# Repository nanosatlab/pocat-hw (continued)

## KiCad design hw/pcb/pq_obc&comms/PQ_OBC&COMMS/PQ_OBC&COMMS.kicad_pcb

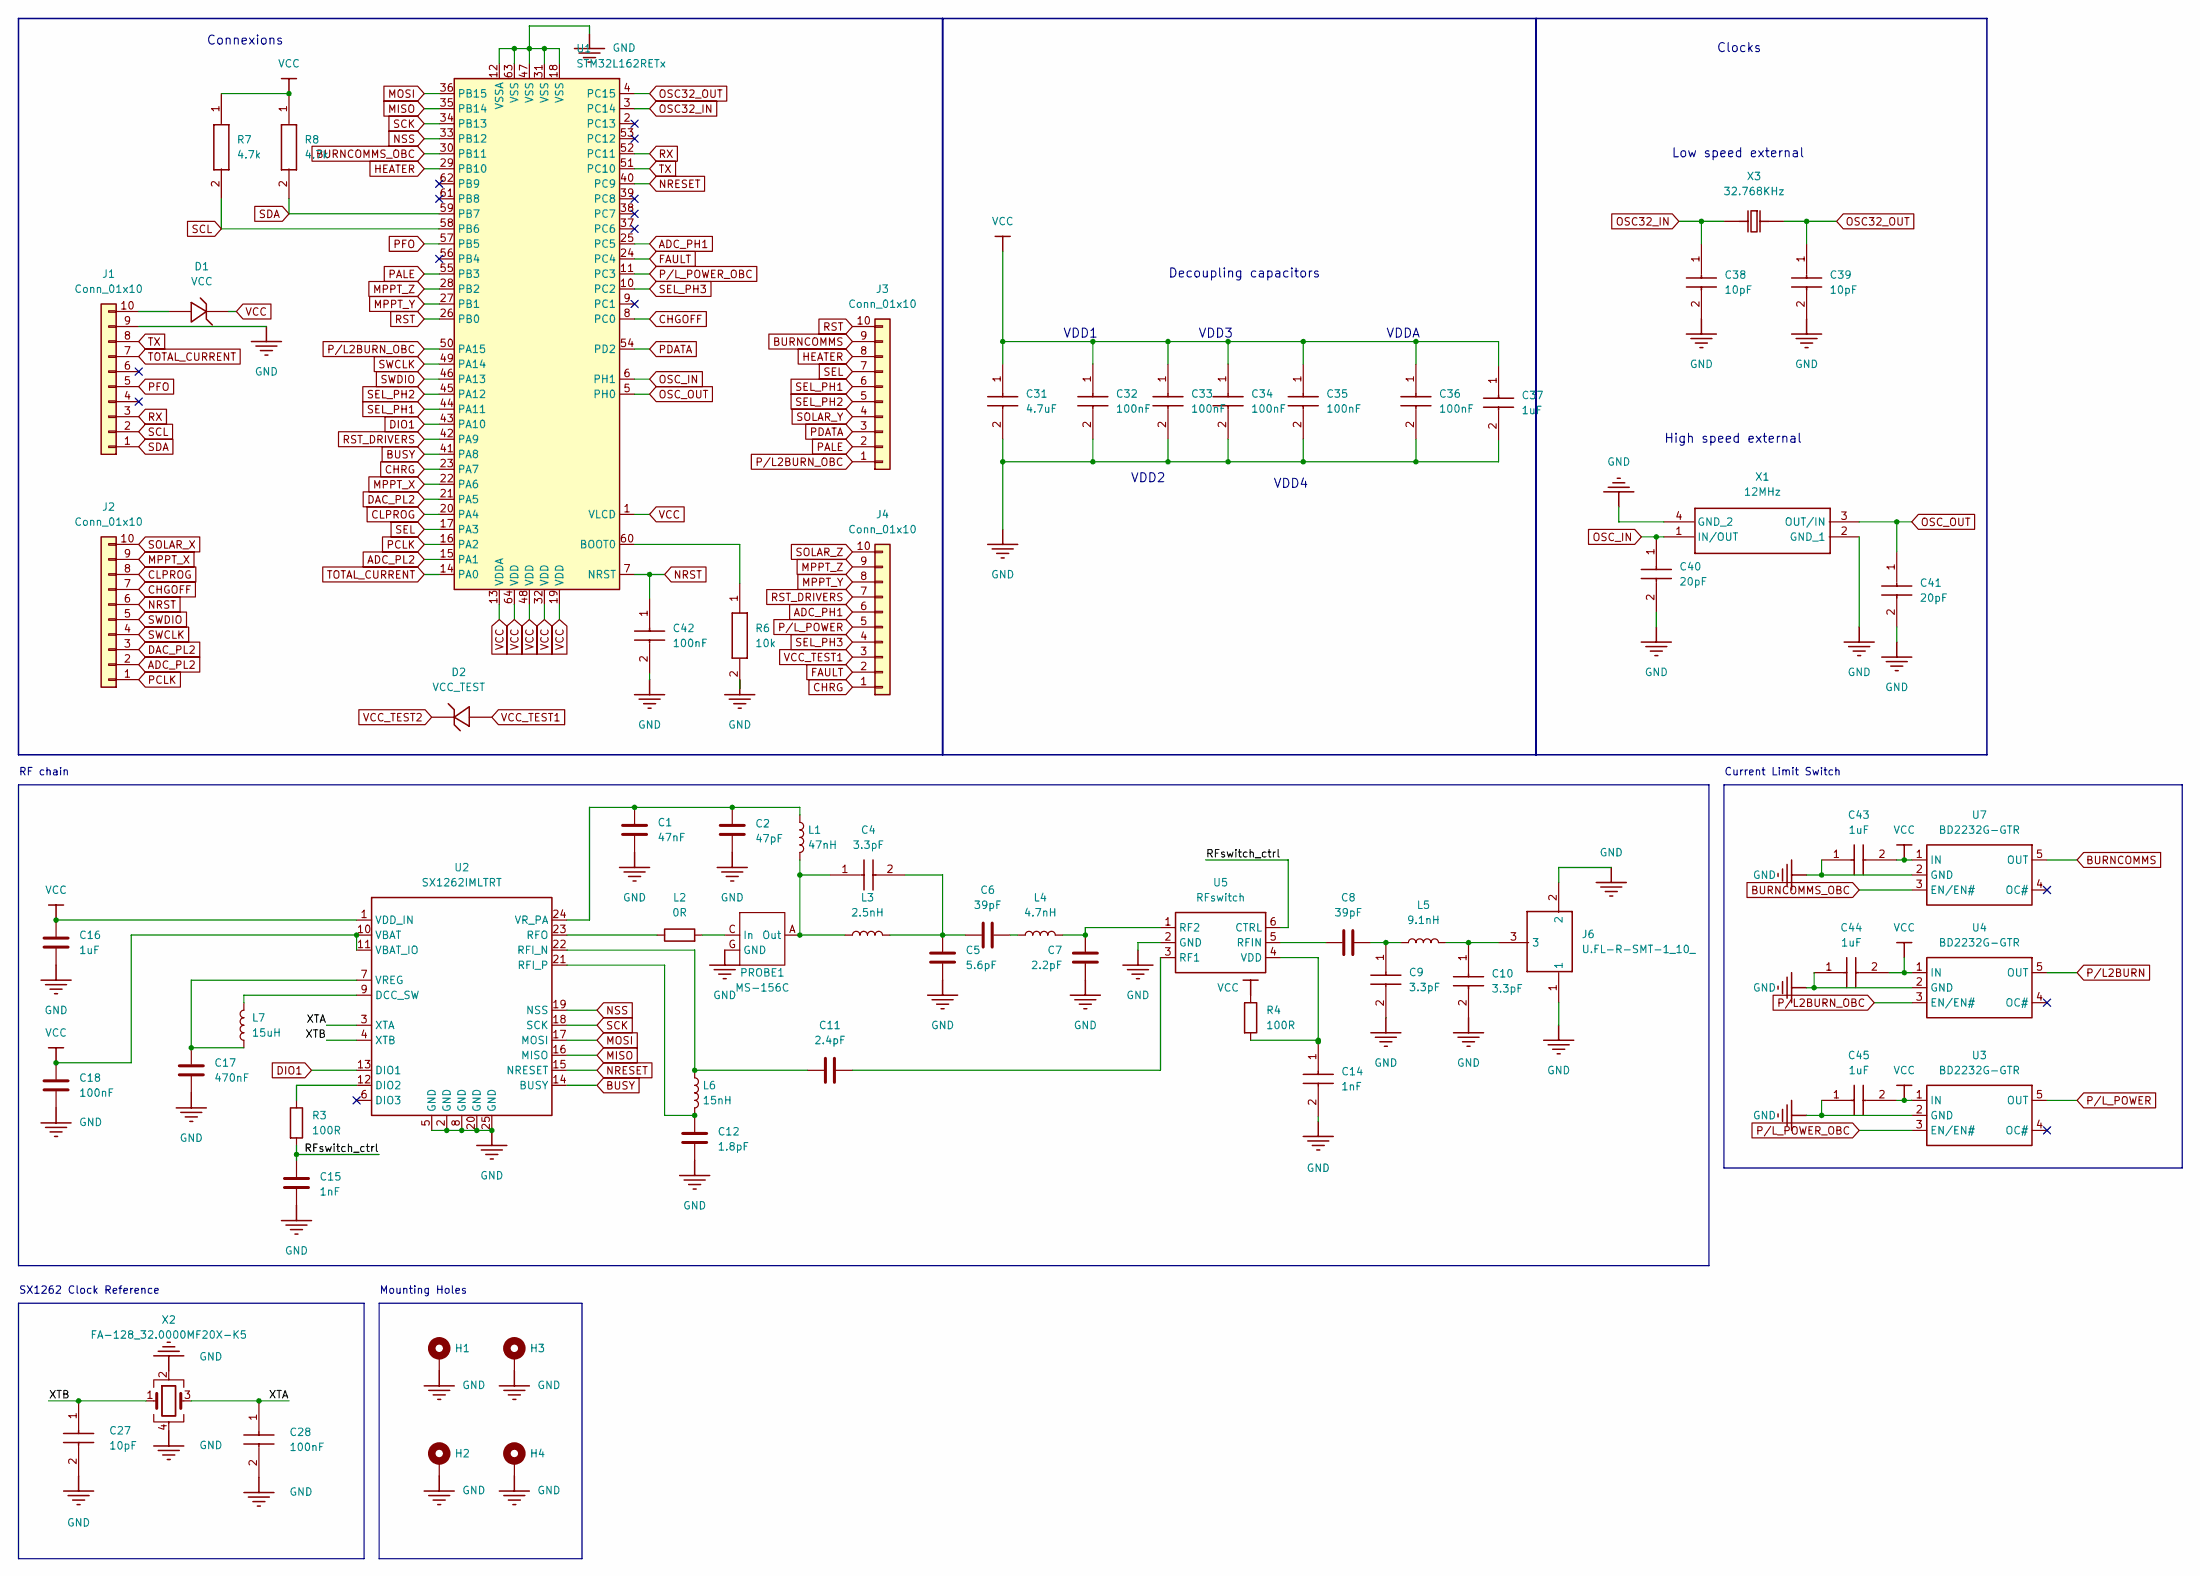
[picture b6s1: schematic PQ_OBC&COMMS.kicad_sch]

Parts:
C1: 47nF
C2: 47pF
C4, C9, C10: 3.3pF
C5: 5.6pF
C6, C8: 39pF
C7: 2.2pF
C11: 2.4pF
C12: 1.8pF
C14, C15: 1nF
C16, C37, C43, C44, C45: 1uF
C17: 470nF
C18, C28, C32, C33, C34, C35, C36, C42: 100nF
C27, C38, C39: 10pF
C31: 4.7uF
C40, C41: 20pF
D1: VCC
D2: VCC_TEST
H1, H2, H3, H4: MountingHole_Pad; MountingHole_3.2mm_M3_Pad
J1, J2, J3, J4: Conn_01x10; PinSocket_1x10_P2.54mm_Vertical
J6: U.FL-R-SMT-1_10_
L1: 47nH
L2: 0R
L3: 2.5nH
L4: 4.7nH
L5: 9.1nH
L6: 15nH
L7: 15uH
PROBE1: MS-156C; CoaxialSwitch_Hirose_MS-156C3_Horizontal
R3, R4: 100R
R6: 10k
R7, R8: 4.7k
U1: STM32L162RETx; LQFP-64_10x10mm_P0.5mm
U2: SX1262IMLTRT
U3, U4, U7: BD2232G-GTR
U5: RFswitch
X1: 12MHz
X2: FA-128_32.0000MF20X-K5
X3: 32.768KHz

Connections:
/RFswitch_ctrl: C15.1, R3.2, U5.6 (CTRL)
/XTA: C28.1, U2.3 (XTA), X2.3
/XTB: C27.1, U2.4 (XTB), X2.1
ADC_PH1: J4.6, U1.25 (PC5)
ADC_PL2: J2.2, U1.15 (PA1)
BURNCOMMS: J3.9, U7.5 (OUT)
BURNCOMMS_OBC: U1.30 (PB11), U7.3 (EN/EN#)
BUSY: U1.41 (PA8), U2.14 (BUSY)
CHGOFF: J2.7, U1.8 (PC0)
CHRG: J4.1, U1.23 (PA7)
CLPROG: J2.8, U1.20 (PA4)
DAC_PL2: J2.3, U1.21 (PA5)
DIO1: U1.43 (PA10), U2.13 (DIO1)
FAULT: J4.2, U1.24 (PC4)
GND: C1.2, C2.2, C5.2, C7.2, C9.2, C10.2, C12.2, C14.2, C15.2, C16.2, C17.2, C18.2, C27.2, C28.2, C31.2, C32.2, C33.2, C34.2, C35.2, C36.2, C37.2, C38.2, C39.2, C40.2, C41.2, C42.2, C43.1, C44.1, C45.1, H1.1, H2.1, H3.1, H4.1, J1.9, J6.1, J6.2, PROBE1.G (GND), R6.2, U1.12 (VSSA), U1.18 (VSS), U1.31 (VSS), U1.47 (VSS), U1.63 (VSS), U2.2 (GND), U2.5 (GND), U2.8 (GND), U2.20 (GND), U2.25 (GND), U3.2 (GND), U4.2 (GND), U5.2 (GND), U7.2 (GND), X1.2 (GND_1), X1.4 (GND_2), X2.2, X2.4
HEATER: J3.8, U1.29 (PB10)
MISO: U1.35 (PB14), U2.16 (MISO)
MOSI: U1.36 (PB15), U2.17 (MOSI)
MPPT_X: J2.9, U1.22 (PA6)
MPPT_Y: J4.8, U1.27 (PB1)
MPPT_Z: J4.9, U1.28 (PB2)
NRESET: U1.40 (PC9), U2.15 (NRESET)
NRST: C42.1, J2.6, U1.7 (NRST)
NSS: U1.33 (PB12), U2.19 (NSS)
unnamed: C4.1, L1.2, L3.1, PROBE1.A (Out)
unnamed: C4.2, C5.1, C6.1, L3.2
unnamed: C6.2, L4.1
unnamed: C8.2, C9.1, L5.1
unnamed: C10.1, J6.3, L5.2
unnamed: C11.1, L6.1, U2.22 (RFI_N)
unnamed: C12.1, L6.2, U2.21 (RFI_P)
unnamed: C14.1, R4.2, U5.4 (VDD)
unnamed: C17.1, L7.1, U2.7 (VREG)
unnamed: D1.2 (A), J1.10
unnamed: L2.2, PROBE1.C (In)
unnamed: R3.1, U2.12 (DIO2)
unnamed: R6.1, U1.60 (BOOT0)
unnamed: L7.2, U2.9 (DCC_SW)
unnamed: L2.1, U2.23 (RFO)
unnamed: C1.1, C2.1, L1.1, U2.24 (VR_PA)
unnamed: C7.1, L4.2, U5.1 (RF2)
unnamed: C11.2, U5.3 (RF1)
unnamed: C8.1, U5.5 (RFIN)
OSC32_IN: C38.1, U1.3 (PC14), X3.1
OSC32_OUT: C39.1, U1.4 (PC15), X3.2
OSC_IN: U1.6 (PH1), X1.1 (IN/OUT)
OSC_OUT: C41.1, U1.5 (PH0), X1.3 (OUT/IN)
PALE: J3.2, U1.55 (PB3)
PCLK: J2.1, U1.16 (PA2)
PDATA: J3.3, U1.54 (PD2)
PFO: J1.5, U1.57 (PB5)
P/L2BURN: U4.5 (OUT)
P/L2BURN_OBC: J3.1, U1.50 (PA15), U4.3 (EN/EN#)
P/L_POWER: J4.5, U3.5 (OUT)
P/L_POWER_OBC: U1.11 (PC3), U3.3 (EN/EN#)
RST: J3.10, U1.26 (PB0)
RST_DRIVERS: J4.7, U1.42 (PA9)
RX: J1.3, U1.52 (PC11)
SCK: U1.34 (PB13), U2.18 (SCK)
SCL: J1.2, R7.2, U1.58 (PB6)
SDA: J1.1, R8.2, U1.59 (PB7)
SEL: J3.7, U1.17 (PA3)
SEL_PH1: J3.6, U1.44 (PA11)
SEL_PH2: J3.5, U1.45 (PA12)
SEL_PH3: J4.4, U1.10 (PC2)
SOLAR_X: J2.10
SOLAR_Y: J3.4
SOLAR_Z: J4.10
SWCLK: J2.4, U1.49 (PA14)
SWDIO: J2.5, U1.46 (PA13)
TOTAL_CURRENT: J1.7, U1.14 (PA0)
TX: J1.8, U1.51 (PC10)
VCC: C16.1, C18.1, C31.1, C32.1, C33.1, C34.1, C35.1, C36.1, C37.1, C43.2, C44.2, C45.2, D1.1 (C), R4.1, R7.1, R8.1, U1.1 (VLCD), U1.13 (VDDA), U1.19 (VDD), U1.32 (VDD), U1.48 (VDD), U1.64 (VDD), U2.1 (VDD_IN), U2.10 (VBAT), U2.11 (VBAT_IO), U3.1 (IN), U4.1 (IN), U7.1 (IN)
VCC_TEST1: D2.2 (A), J4.3
VCC_TEST2: D2.1 (C)

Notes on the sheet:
VDD2
Decoupling capacitors
RF chain
SX1262 Clock Reference
VDD1
Clocks
Low speed external
Connexions
VDD3
VDDA
High speed external
Mounting Holes
VDD4
Current Limit Switch

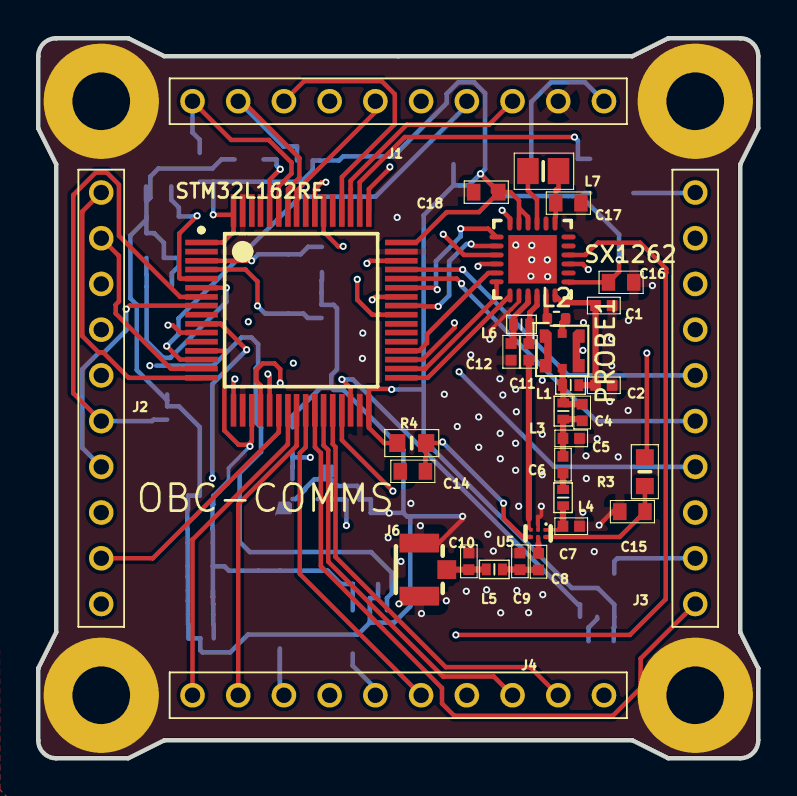
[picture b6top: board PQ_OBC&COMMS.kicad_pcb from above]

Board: 4 copper layers, 40.0 x 40.0 mm, 66 parts (0 on the bottom side), 70 nets.
